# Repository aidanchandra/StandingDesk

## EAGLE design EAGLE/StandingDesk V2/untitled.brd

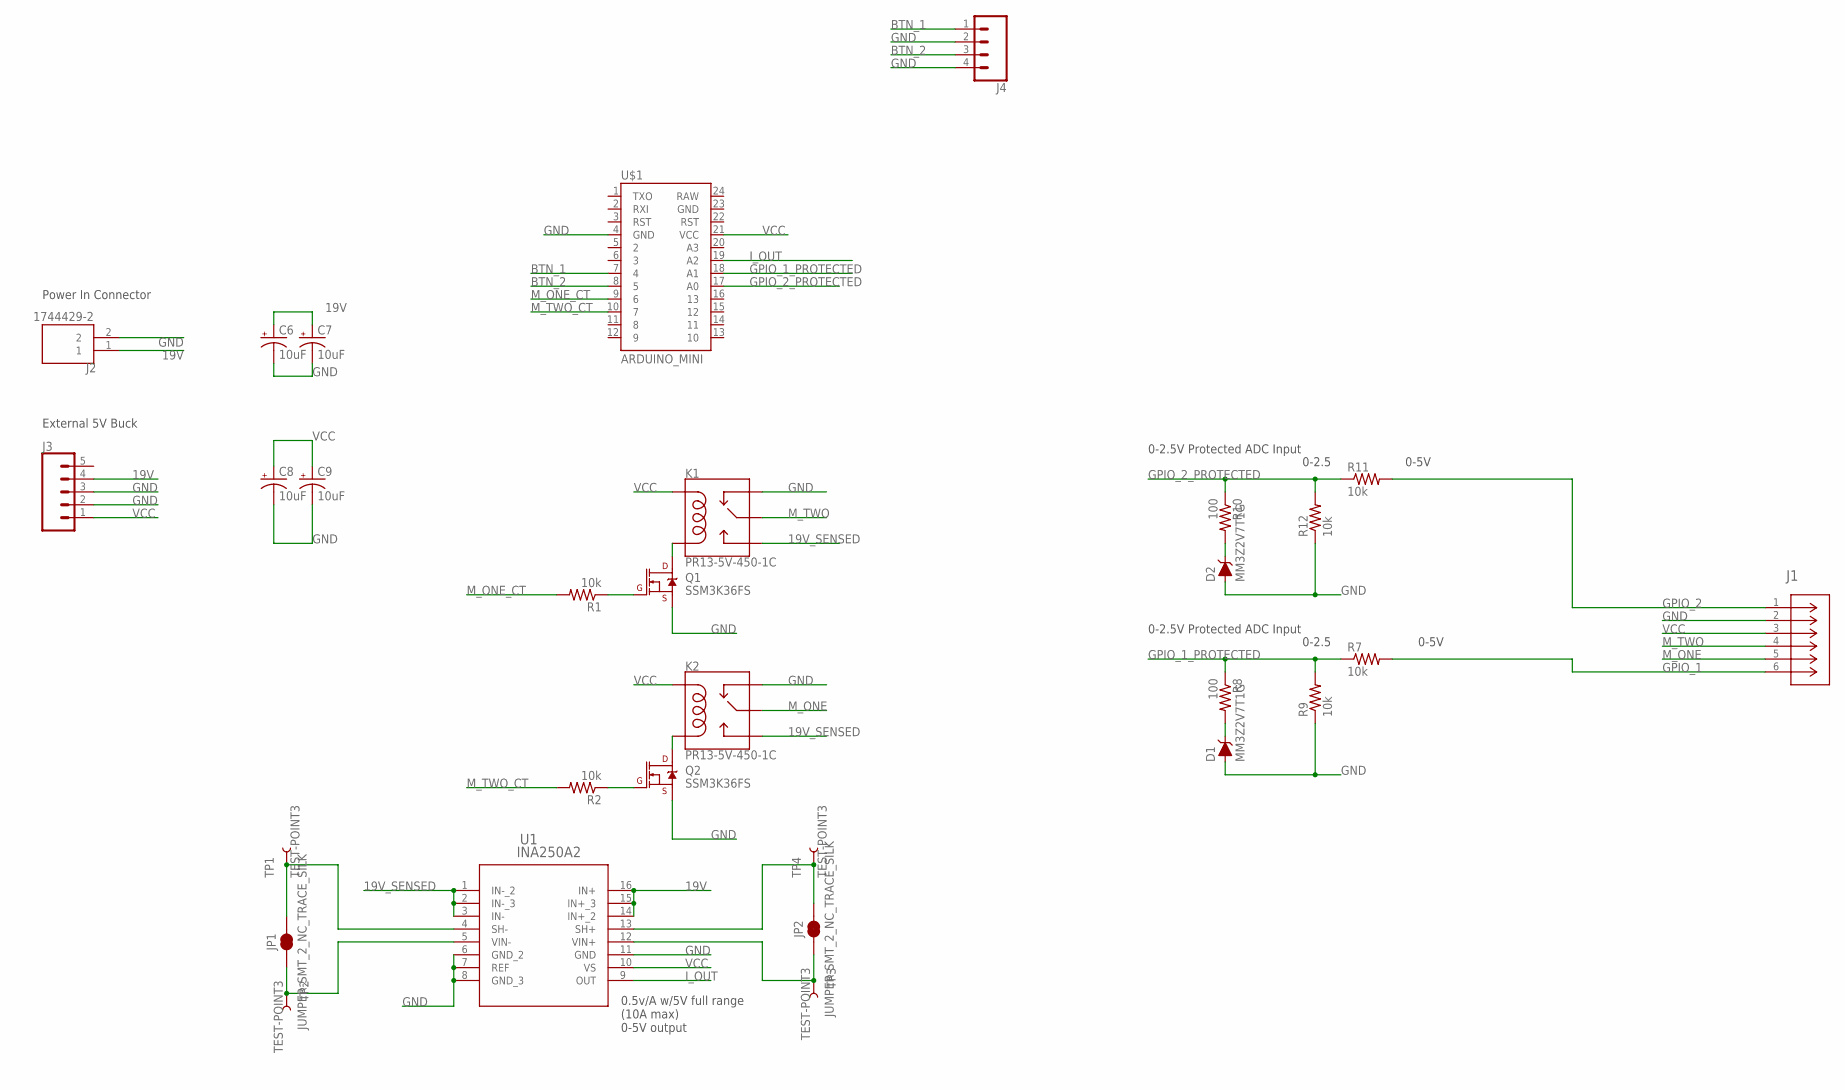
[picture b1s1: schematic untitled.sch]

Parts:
C6, C7, C8, C9: 10uF; E2,5-6
D1, D2: MM3Z2V7T1G; SOD-323
J1: 39301060; CON_39301060
J2: 1744429-2; TE_1744429-2
J3: CONN_05; 1X05
J4: CONN_041X04_NO_SILK; 1X04_NO_SILK
JP1, JP2: JUMPER-SMT_2_NC_TRACE_SILK; SMT-JUMPER_2_NC_TRACE_SILK
K1, K2: PR13-5V-450-1C; RELAY_G5LE
Q1, Q2: SSM3K36FS; SOT23-3
R1, R2, R7, R9, R11, R12: 10k; R0805
R8, R10: 100; R0805
TP1, TP2, TP3, TP4: TEST-POINT3; PAD.03X.03
U1: INA250A2; PW16_TEX-M
U$1: ARDUINO_MINI

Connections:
19V: C6.+, C7.+, J2.1, J3.4, U1.14 (IN+_2), U1.15 (IN+_3), U1.16 (IN+)
19V_SENSED: K1.3 (NO), K2.3 (NO), U1.1 (IN-_2), U1.2 (IN-_3), U1.3 (IN-)
BTN_1: J4.1, U$1.7 (4)
BTN_2: J4.3, U$1.8 (5)
GND: C6.-, C7.-, C8.-, C9.-, D1.A, D2.A, J1.2, J2.2, J3.2, J3.3, J4.2, J4.4, K1.4 (NC), K2.4 (NC), Q1.2 (S), Q2.2 (S), R9.1, R12.1, U1.6 (GND_2), U1.7 (REF), U1.8 (GND_3), U1.11 (GND), U$1.4 (GND)
GPIO_1: J1.6, R7.2
GPIO_1_PROTECTED: R7.1, R8.1, R9.2, U$1.18 (A1)
GPIO_2: J1.1, R11.2
GPIO_2_PROTECTED: R10.1, R11.1, R12.2, U$1.17 (A0)
I_OUT: U1.9 (OUT), U$1.19 (A2)
M_ONE: J1.5, K2.1 (MAIN)
M_ONE_CT: R1.2, U$1.9 (6)
M_TWO: J1.4, K1.1 (MAIN)
M_TWO_CT: R2.2, U$1.10 (7)
unnamed: JP1.1, TP2.1, U1.5 (VIN-)
unnamed: JP1.2, TP1.1, U1.4 (SH-)
unnamed: JP2.2, TP4.1, U1.13 (SH+)
unnamed: K1.5 (COIL2), Q1.3 (D)
unnamed: K2.5 (COIL2), Q2.3 (D)
unnamed: Q2.1 (G), R2.1
unnamed: D1.C, R8.2
unnamed: Q1.1 (G), R1.1
unnamed: D2.C, R10.2
unnamed: JP2.1, TP3.1, U1.12 (VIN+)
VCC: C8.+, C9.+, J1.3, J3.1, K1.2 (COIL1), K2.2 (COIL1), U1.10 (VS), U$1.21 (VCC)

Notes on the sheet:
0-2.5V Protected ADC Input
Power In Connector
External 5V Buck
0-5V
0-2.5
0.5v/A w/5V full range (10A max) 0-5V output

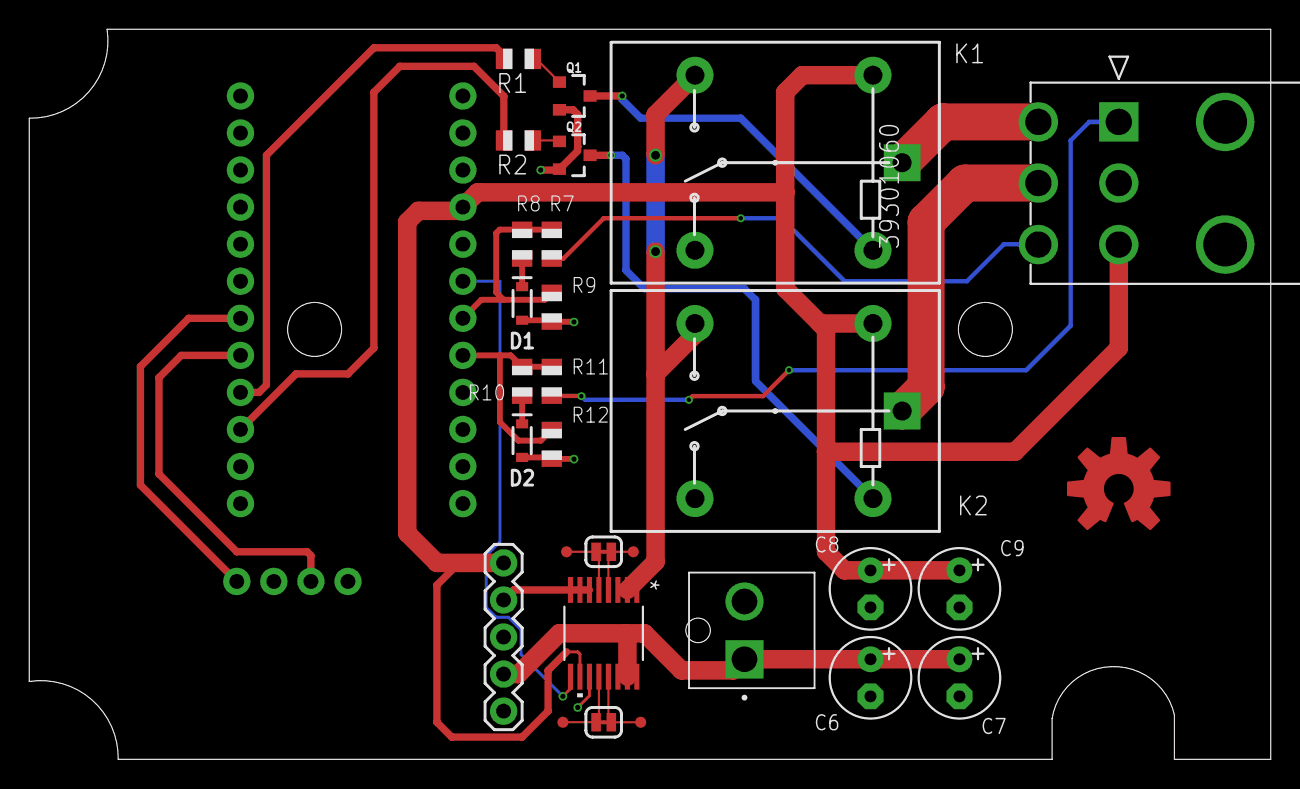
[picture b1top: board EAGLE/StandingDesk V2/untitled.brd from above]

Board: 2 copper layers, 85.1 x 50.0 mm, 31 parts (0 on the bottom side), 25 nets.

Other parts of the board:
U$2: OSHW-LOGO-L_COPPER

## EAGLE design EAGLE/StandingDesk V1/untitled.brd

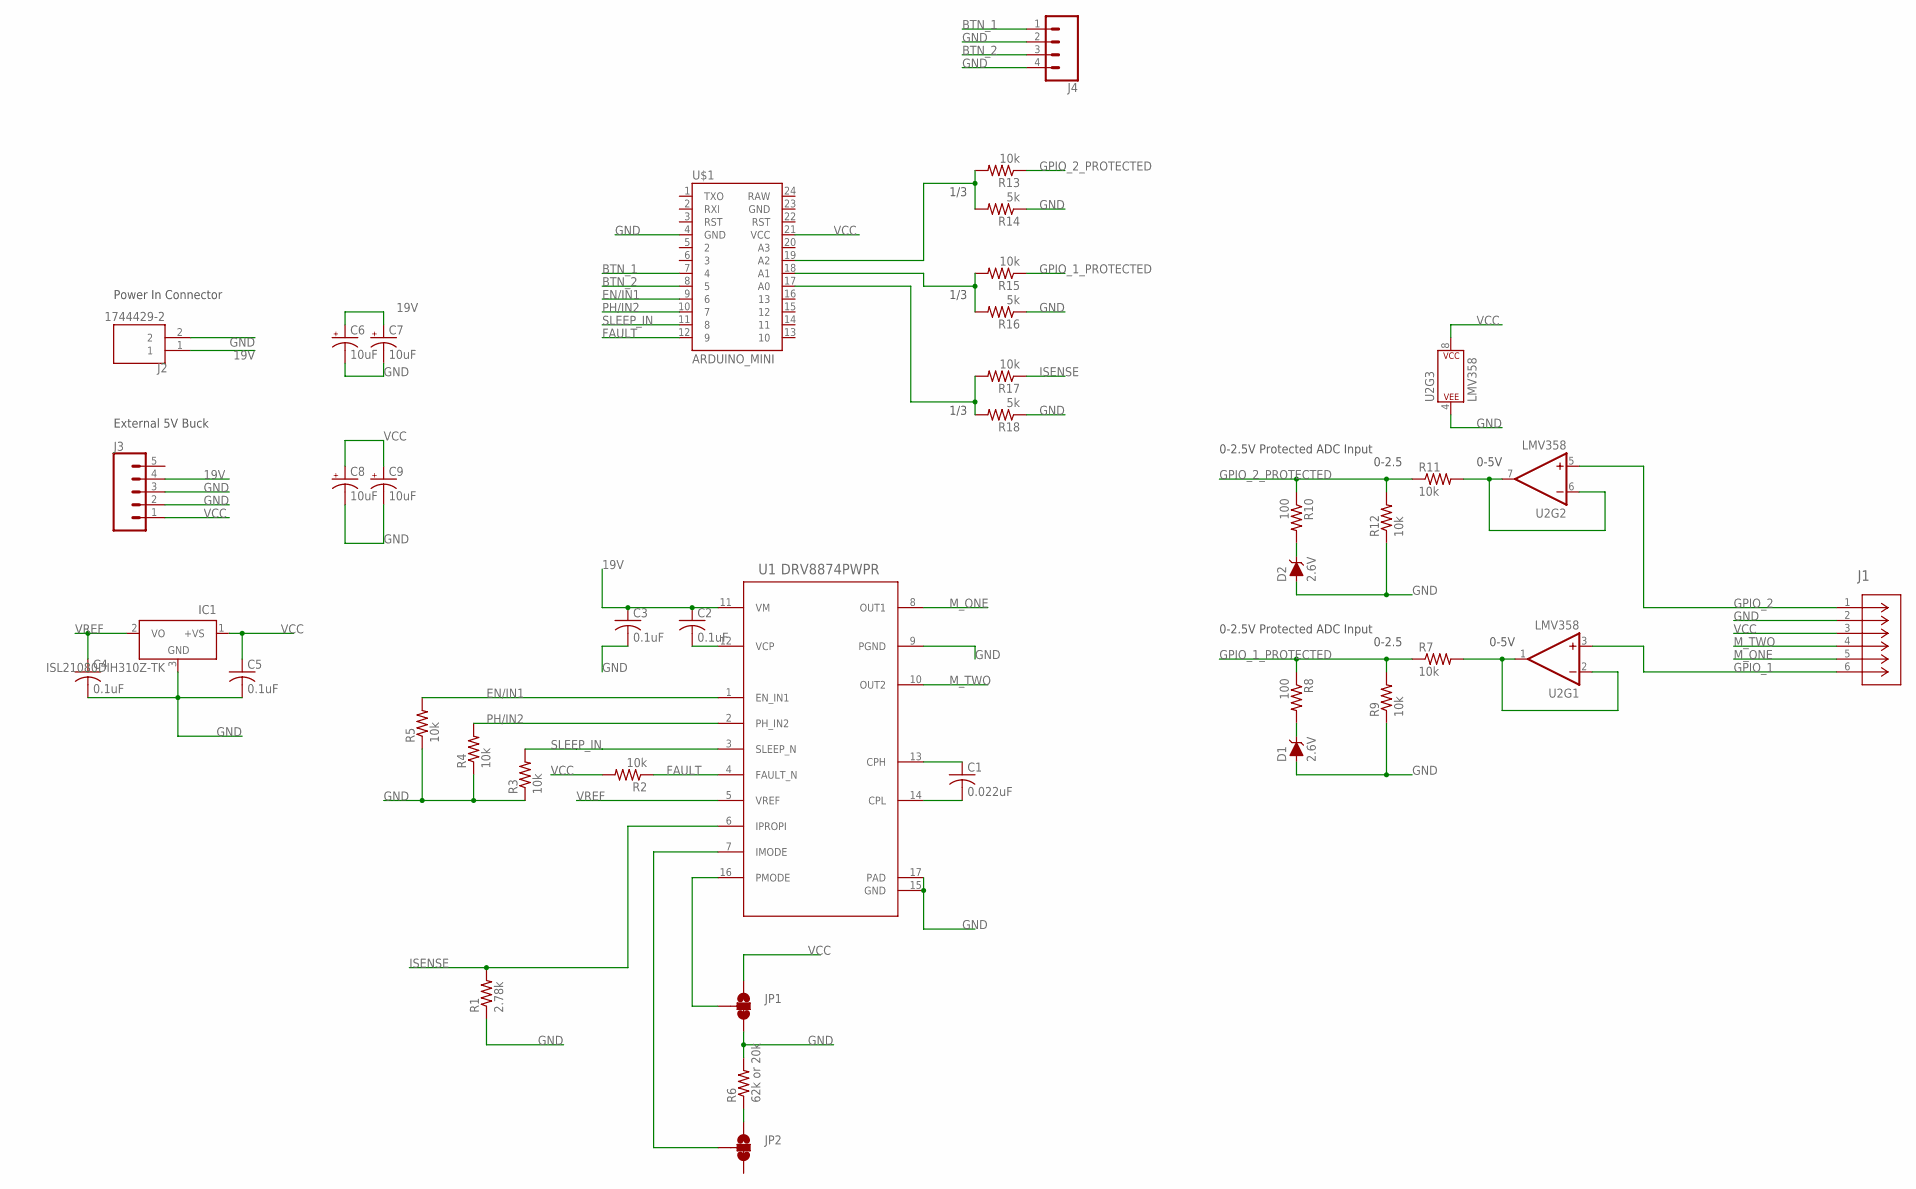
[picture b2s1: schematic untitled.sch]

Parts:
C1: 0.022uF; C0805K
C2, C3, C4, C5: 0.1uF; C0805K
C6, C7, C8, C9: 10uF; E2,5-6
D1, D2: 2.6V; SOD-323
IC1: ISL21080DIH310Z-TK; SOT23
J1: 39301060; CON_39301060
J2: 1744429-2; TE_1744429-2
J3: CONN_05; 1X05
J4: CONN_041X04_NO_SILK; 1X04_NO_SILK
JP1, JP2: JUMPER-SMT_3_1-NC_TRACE_SILK; SMT-JUMPER_3_1-NC_TRACE_SILK
R1: 2.78k; R0805
R2, R3, R4, R5, R7, R9, R11, R12, R13, R15, R17: 10k; R0805
R6: 62k or 20k; R0805
R8, R10: 100; R0805
R14, R16, R18: 5k; R0805
U1: DRV8874PWPR; PWP0016J_N
U2: LMV358; SO08
U$1: ARDUINO_MINI

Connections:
19V: C2.1, C3.1, C6.+, C7.+, J2.1, J3.4, U1.11 (VM)
BTN_1: J4.1, U$1.7 (4)
BTN_2: J4.3, U$1.8 (5)
EN/IN1: R5.2, U1.1 (EN_IN1), U$1.9 (6)
FAULT: R2.1, U1.4 (FAULT_N), U$1.12 (9)
GND: C3.2, C4.2, C5.2, C6.-, C7.-, C8.-, C9.-, D1.A, D2.A, IC1.3 (GND), J1.2, J2.2, J3.2, J3.3, J4.2, J4.4, JP1.3, R1.1, R3.1, R4.1, R5.1, R6.2, R9.1, R12.1, R14.1, R16.1, R18.1, U1.9 (PGND), U1.15 (GND), U1.17 (PAD), U2.4 (P$V-), U$1.4 (GND)
GPIO_1: J1.6, U2.3 (+IN)
GPIO_1_PROTECTED: R7.1, R8.1, R9.2, R15.1
GPIO_2: J1.1, U2.5 (+IN)
GPIO_2_PROTECTED: R10.1, R11.1, R12.2, R13.1
ISENSE: R1.2, R17.1, U1.6 (IPROPI)
M_ONE: J1.5, U1.8 (OUT1)
M_TWO: J1.4, U1.10 (OUT2)
unnamed: C1.2, U1.14 (CPL)
unnamed: C1.1, U1.13 (CPH)
unnamed: R17.2, R18.2, U$1.17 (A0)
unnamed: C2.2, U1.12 (VCP)
unnamed: JP1.2, U1.16 (PMODE)
unnamed: R7.2, U2.1 (OUT), U2.2 (-IN)
unnamed: D1.C, R8.2
unnamed: R11.2, U2.6 (-IN), U2.7 (OUT)
unnamed: D2.C, R10.2
unnamed: JP2.2, U1.7 (IMODE)
unnamed: JP2.1, R6.1
unnamed: R13.2, R14.2, U$1.19 (A2)
unnamed: R15.2, R16.2, U$1.18 (A1)
PH/IN2: R4.2, U1.2 (PH_IN2), U$1.10 (7)
SLEEP_IN: R3.2, U1.3 (SLEEP_N), U$1.11 (8)
VCC: C5.1, C8.+, C9.+, IC1.1 (+VS), J1.3, J3.1, JP1.1, R2.2, U2.8 (P$V+), U$1.21 (VCC)
VREF: C4.1, IC1.2 (VO), U1.5 (VREF)

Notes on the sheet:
0-2.5V Protected ADC Input
Power In Connector
External 5V Buck
0-5V
0-2.5
1/3

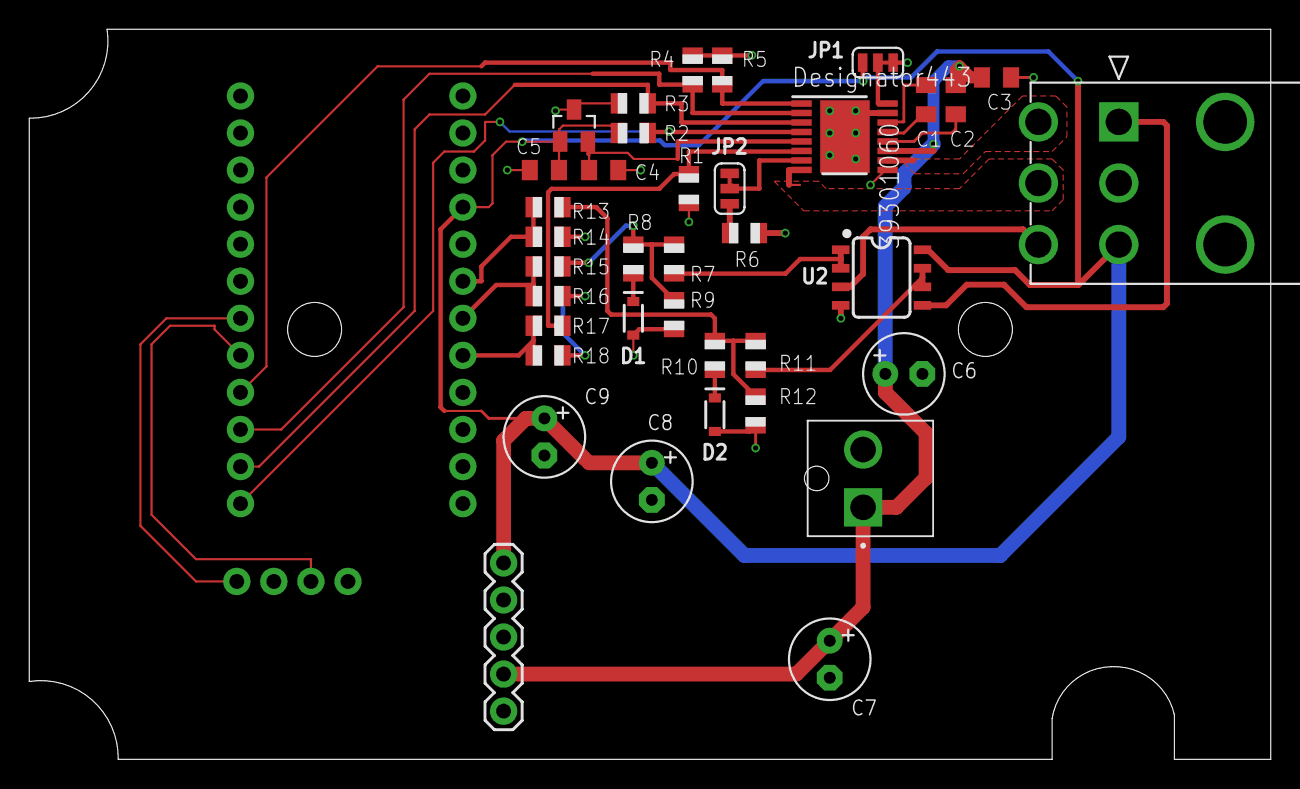
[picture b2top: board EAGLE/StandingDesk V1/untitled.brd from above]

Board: 2 copper layers, 85.1 x 50.0 mm, 39 parts (0 on the bottom side), 30 nets.

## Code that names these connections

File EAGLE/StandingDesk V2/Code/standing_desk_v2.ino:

#include <EEPROM.h>

#define DEBUG 1

#define BTN_1 4
#define BTN_2 5
#define m_one_ct 6
#define m_two_ct 7

#define currentsense A2
#define steppin 3

#define top_steps 2250

float zeroReference = 0;
float curCurrent = 0;

int topPreset = -1;
int botPreset = -1;

bool movementDirection = 0;
bool isCalibrated = false;
long steps = 2250;

void setup() {
  if(DEBUG) Serial.begin(9600);
  pinMode(BTN_1, INPUT_PULLUP);
  pinMode(BTN_2, INPUT_PULLUP);

  pinMode(m_one_ct, OUTPUT);
  pinMode(m_two_ct, OUTPUT);

  attachInterrupt(digitalPinToInterrupt(steppin), step_counter, RISING);

  zeroReference = analogRead(currentsense);
  curCurrent = analogRead(currentsense);
}

void step_counter(){
  if(movementDirection) steps +=1;
  else steps-=1;
}

#define HOLD_THRESHOLD 100
#define IGNORE_THRESHOLD 400
#define HOLD_TO_DOUBLE_THRESHOLD 150
void loop() {
  
  //Wait for a button press
  while(!btnOnePressed() && !btnTwoPressed());//Serial.println("Waiting for first press");
  unsigned long startTime = millis();
  bool bOneInitial = btnOnePressed();
  bool bTwoInitial = btnTwoPressed();
  
  delay(HOLD_THRESHOLD);

  while((!btnOnePressed() && !btnTwoPressed()) && (millis()-startTime < IGNORE_THRESHOLD + 100));//Serial.println("Waiting for second press");
  unsigned long endTime = millis();
  bool bOneFinal = btnOnePressed();
  bool bTwoFinal = btnTwoPressed();
  
  unsigned long elapsedTime = endTime - startTime;
  if(elapsedTime > IGNORE_THRESHOLD){
    Serial.println("Too long between presses... ignoring");
  }
  else{

    if(bTwoFinal == 1 && bOneFinal == 1){
      int elapsedTime = 0;
      while(btnOnePressed() && btnTwoPressed() && elapsedTime <= 200){
        elapsedTime++;
        delay(1);
      }
      if(elapsedTime > 200){
        Serial.println("Bottom set");
        steps = 0;
        delay(500);
        motorForward();
        delay(200);
        motorStop();
      }
      else{
        if(steps > topPreset){ //If steps > top preset -> this pos is top prest
          botPreset = topPreset;
          topPreset = steps;
        }
        else{
          botPreset = steps;
        }
        if(botPreset < 15){
          botPreset = 15;
        }
        if(topPreset < 15){
          topPreset = 15;
        }
        if(botPreset > 2250){
          botPreset = 2250;
        }
        if(topPreset > 2250){
          topPreset = 2250;
        }
        Serial.println("Custom set");
      }
    }
    else if(elapsedTime > HOLD_TO_DOUBLE_THRESHOLD){
      Serial.print("Double Press: ");
      if(bTwoFinal == 1 && bOneFinal == 0){
        Serial.println("Left Button");
        Serial.print("Going to bottom preset ");
        Serial.println(botPreset);
        goTo(botPreset);
      }
      else if(bTwoFinal == 0 && bOneFinal == 1){
        Serial.println("Right button");
        Serial.print("Going to top preset ");
        Serial.println(topPreset);
        goTo(topPreset);
      }
    }
    else{
      Serial.print("Single/Hold Press ");
      if(bTwoFinal == 1 && bOneFinal == 0){
        Serial.println("Left Button - move downwards");
        while(btnTwoPressed()!=0 && steps >= 15)
          motorBackward();
        motorStop();
        if(!(steps >= 10)) Serial.println("At bottom limit");
      }
      else if(bTwoFinal == 0 && bOneFinal == 1){
        Serial.println("Right button - move forwards");
        while(btnOnePressed()!=0 && steps < top_steps)
          motorForward();
        motorStop();
        if(!(steps < top_steps)) Serial.println("At top limit");
      }
    }
  }
  Serial.println("-------------");
  while(btnOnePressed()!=0 || btnTwoPressed()!=0);
  Serial.println("Done");
  motorStop();
}

int difference(int place){
  //Returns a negative number if current place is less than steps - WE ARE BELOW REQUESTED
  //Returns a positive number if current place is greater than steps - WE ARE ABOVE REQUESTED
  return (place - steps);
}

void goTo(int place){
  if(steps < place){ //current pos is below - need to go up
    Serial.print("Driving up to ");
    Serial.println(place);
    while(steps < place){
      motorForward();
    }
    motorStop();
  }
  else{
    Serial.print("Driving down to ");
    Serial.println(place);
    while(steps > place){
      motorBackward();
    }
    motorStop();
  }
  
}

bool btnOnePressed(){
  return (digitalRead(BTN_1) == LOW);
}
bool btnTwoPressed(){
  return (digitalRead(BTN_2) == LOW);
}

void driveUpward(){
  if(steps <= top_steps){
    motorForward();
  }
  else{
    Serial.println("At limit!");
  }
}
void driveDownward(){
  Serial.println("Running");
  if(steps >= 20){
    motorBackward();
  }
  else{
    Serial.println("At limit!");
  }
}
void motorForward(){
      movementDirection = 1;
      digitalWrite(m_two_ct, HIGH);
      digitalWrite(m_one_ct, LOW);
}
void motorBackward(){
    movementDirection = 0;
    digitalWrite(m_two_ct, LOW);
    digitalWrite(m_one_ct, HIGH);
}
void motorStop(){
  digitalWrite(m_two_ct, LOW);
  digitalWrite(m_one_ct, LOW);
  delay(100);
  zeroReference = analogRead(currentsense);
}

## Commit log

2022-09-27 Adding files
2022-09-28 Eagle work
2023-09-20 Finally adding everything else
2023-09-30 work

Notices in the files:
parts and their libraries:
SparkFun-DiscreteSemi: Licensing: Creative Commons ShareAlike 4.0 International - https://creativecommons.org/licenses/by-sa/4.0
COPYRIGHT: Copyright (C) 2022 Ultra Librarian. All rights reserved.
